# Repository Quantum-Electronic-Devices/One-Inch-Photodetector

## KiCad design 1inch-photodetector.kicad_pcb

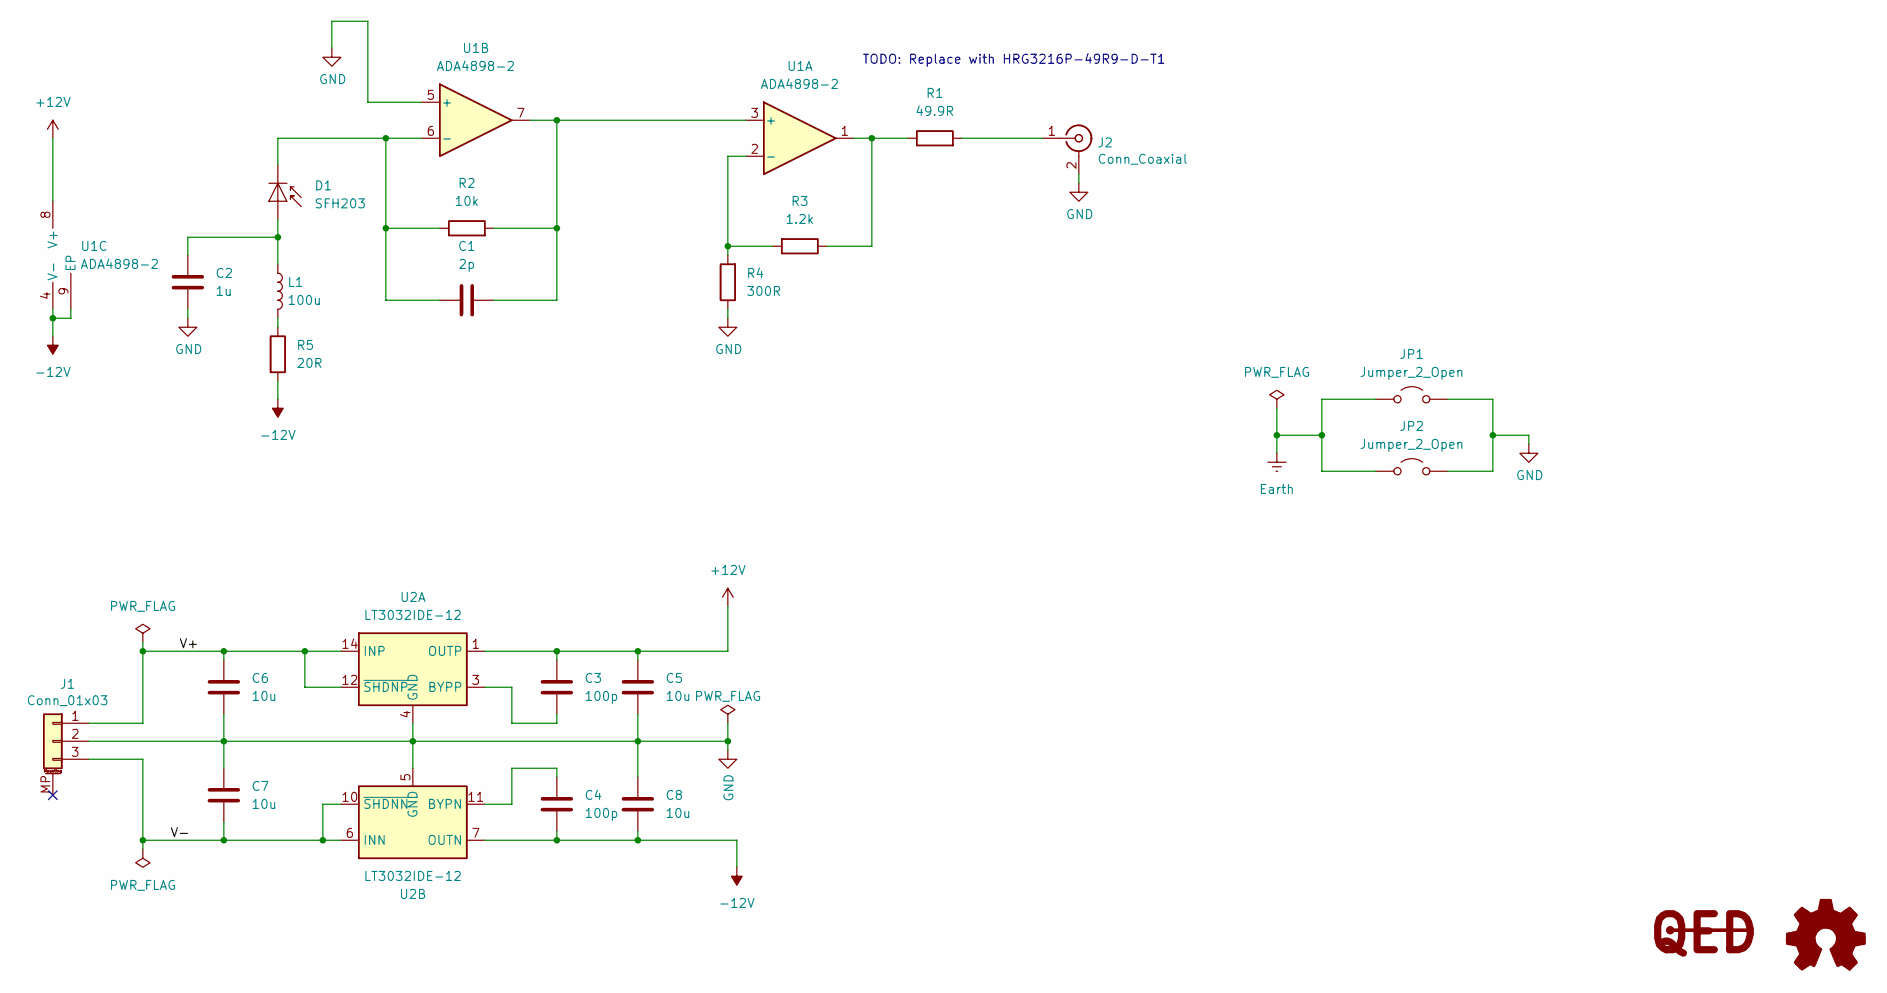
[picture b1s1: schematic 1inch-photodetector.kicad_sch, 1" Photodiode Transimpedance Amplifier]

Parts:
C1: 2p; C_0603_1608Metric
C2: 1u; C_0603_1608Metric
C3, C4: 100p; C_0603_1608Metric
C5, C6, C7, C8: 10u; C_0805_2012Metric
D1: SFH203; LED_D5.0mm_IRGrey
J1: Conn_01x03; Molex_PicoBlade_53398-0371_1x03-1MP_P1.25mm_Vertical
J2: Conn_Coaxial; SMP_TE_CONSMP001-SMD-G-T_Vertical
JP1, JP2: Jumper_2_Open; R_0402_1005Metric
L1: 100u; L_0805_2012Metric
LOGO1: Logo_Open_Hardware_Large; OSHW-Logo_7.5x8mm_SilkScreen
R1: 49.9R; R_1206_3216Metric
R2: 10k; R_0603_1608Metric
R3: 1.2k; R_0603_1608Metric
R4: 300R; R_0603_1608Metric
R5: 20R; R_0603_1608Metric
SYM1: Logo_QED; QED-logo_small
U1: ADA4898-2; SOIC-8-1EP_3.9x4.9mm_P1.27mm_EP2.41x3.81mm
U2: LT3032IDE-12; Linear_DE14MA

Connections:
+12V: C3.1, C5.1, U1.8 (V+), U2.1 (OUTP)
-12V: C4.2, C8.2, R5.2, U1.4 (V-), U1.9 (EP), U2.7 (OUTN)
/V+: C6.1, J1.1, U2.12 (~SHDNP), U2.14 (INP)
/V-: C7.2, J1.3, U2.6 (INN), U2.9 (INN), U2.10 (~SHDNN)
Earth: JP1.1 (A), JP2.1 (A)
GND: C2.2, C5.2, C6.2, C7.1, C8.1, J1.2, J2.2 (Ext), JP1.2 (B), JP2.2 (B), R4.1, U1.5 (+), U2.4 (GND), U2.5 (GND)
unnamed: C2.1, D1.2 (A), L1.1
unnamed: C1.1, D1.1 (K), R2.1, U1.6 (-)
unnamed: J2.1 (In), R1.2
unnamed: L1.2, R5.1
unnamed: R1.1, R3.1, U1.1
unnamed: C1.2, R2.2, U1.3 (+), U1.7
unnamed: R3.2, R4.2, U1.2 (-)
unnamed: C3.2, U2.3 (BYPP)
unnamed: C4.1, U2.11 (BYPN)

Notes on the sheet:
TODO: Replace with HRG3216P-49R9-D-T1

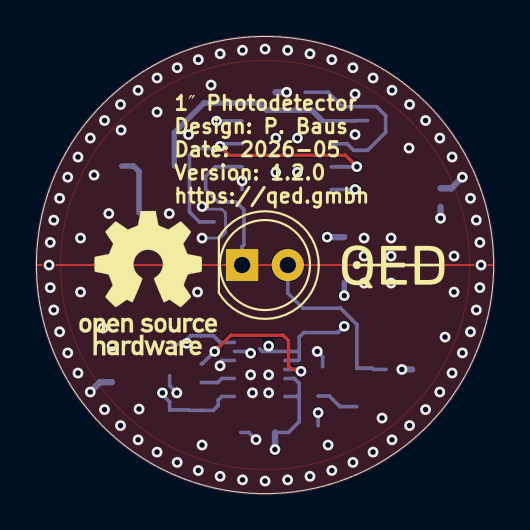
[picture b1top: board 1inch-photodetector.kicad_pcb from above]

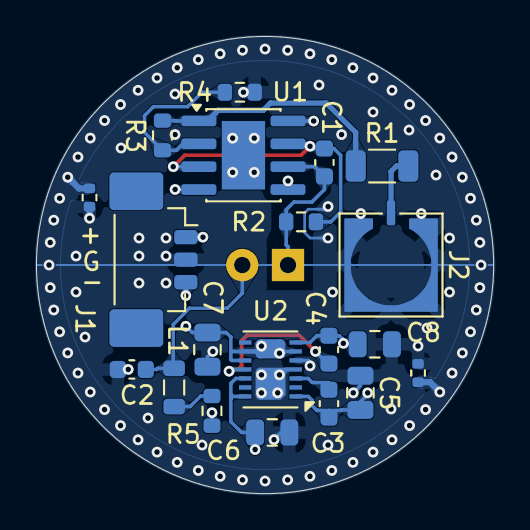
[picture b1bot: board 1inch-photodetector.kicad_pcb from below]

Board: 4 copper layers, 25.4 x 25.4 mm, 23 parts (20 on the bottom side), 15 nets.

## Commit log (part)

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2025-11-25 Bump KiBot to v9
2025-11-25 Cleanup
2025-11-25 [gha] Bump actions/download-artifact from 4 to 6
    Bumps [actions/download-artifact](https://github.com/actions/download-artifact) from 4 to 6.
    - [Release notes](https://github.com/actions/download-artifact/releases)
    - [Commits](https://github.com/actions/download-artifact/compare/v4...v6)
    ---
    updated-dependencies:
    - dependency-name: actions/download-artifact
2025-11-25 Update logo
2025-11-25 [gha] Bump actions/upload-artifact from 4 to 5
    Bumps [actions/upload-artifact](https://github.com/actions/upload-artifact) from 4 to 5.
    - [Release notes](https://github.com/actions/upload-artifact/releases)
    - [Commits](https://github.com/actions/upload-artifact/compare/v4...v5)
    ---
    updated-dependencies:
    - dependency-name: actions/upload-artifact
2025-11-25 Changed QED logo to polygon to make it independent of the font of the host system
2025-11-25 Add copyright notice to logo
2025-11-25 Remove QED text from silkscreen
2025-11-25 Update logo copyright
2025-11-25 Added QED URL to version text
2025-12-12 [gha] Bump actions/upload-artifact from 5 to 6
    Bumps [actions/upload-artifact](https://github.com/actions/upload-artifact) from 5 to 6.
    - [Release notes](https://github.com/actions/upload-artifact/releases)
    - [Commits](https://github.com/actions/upload-artifact/compare/v5...v6)
    ---
    updated-dependencies:
    - dependency-name: actions/upload-artifact
2025-12-12 [gha] Bump actions/download-artifact from 6 to 7
    Bumps [actions/download-artifact](https://github.com/actions/download-artifact) from 6 to 7.
    - [Release notes](https://github.com/actions/download-artifact/releases)
    - [Commits](https://github.com/actions/download-artifact/compare/v6...v7)
    ---
    updated-dependencies:
    - dependency-name: actions/download-artifact
2025-12-17 Bump libraries from `ba5563d` to `d79317d`
    Bumps [libraries](https://github.com/PatrickBaus/KiCad-libraries) from `ba5563d` to `d79317d`.
    - [Commits](https://github.com/PatrickBaus/KiCad-libraries/compare/ba5563d66c23dea06d561adcb039ddac5a03efdf...d79317d926704a58090a36fac06bfafa731a048b)
    ---
    updated-dependencies:
    - dependency-name: libraries
    dependency-version: d79317d926704a58090a36fac06bfafa731a048b
2026-02-26 [gha] Bump actions/upload-artifact from 5 to 7
    Bumps [actions/upload-artifact](https://github.com/actions/upload-artifact) from 5 to 7.
    - [Release notes](https://github.com/actions/upload-artifact/releases)
    - [Commits](https://github.com/actions/upload-artifact/compare/v5...v7)
    ---
    updated-dependencies:
    - dependency-name: actions/upload-artifact
2026-02-26 [gha] Bump actions/download-artifact from 6 to 8
    Bumps [actions/download-artifact](https://github.com/actions/download-artifact) from 6 to 8.
    - [Release notes](https://github.com/actions/download-artifact/releases)
    - [Commits](https://github.com/actions/download-artifact/compare/v6...v8)
    ---
    updated-dependencies:
    - dependency-name: actions/download-artifact
2026-02-28 Bump footprints to latest
2026-02-28 Add comments regarding tolerances
2026-02-28 Fixed white spaces
2026-02-28 Disconnect GND from Earth by default (#10)
    * Removed GND-Earth connection
    - Added optional jumpers to connect GND to Earth
    - Added more ground stitching vias
    * Increased size to 25.4 mm
    * Added comments regarding tolerances
2026-02-28 [gha] Bump actions/upload-artifact from 5 to 7 (#8)
    Bumps [actions/upload-artifact](https://github.com/actions/upload-artifact) from 5 to 7.
    - [Release notes](https://github.com/actions/upload-artifact/releases)
    - [Commits](https://github.com/actions/upload-artifact/compare/v5...v7)
    ---
    updated-dependencies:
    - dependency-name: actions/upload-artifact
2026-02-28 Bump libraries from `ba5563d` to `4179135` (#7)
    Bumps [libraries](https://github.com/PatrickBaus/KiCad-libraries) from `ba5563d` to `4179135`.
    - [Commits](https://github.com/PatrickBaus/KiCad-libraries/compare/ba5563d66c23dea06d561adcb039ddac5a03efdf...41791358010d2de5d2401e25bd30de257630acf6)
    ---
    updated-dependencies:
    - dependency-name: libraries
    dependency-version: 41791358010d2de5d2401e25bd30de257630acf6
2026-02-28 Added stackup to gerber files
2026-02-28 Added stackup to gerber files (#11)
2026-02-28 Bump version to 1.1.0
2026-03-01 Fix intermittend GHA ref_name is empty issue. See https://github.com/actions/runner/issues/2788
2026-03-01 Cleanup/remove old refs (#13)
    * Removed TODOs that where done
    - Fixed R1 MFN
    * Added gerber_files folder to gitignore
2026-03-02 Fix stackup. An incorrect stackup was given. Changed to PCBWay/JLCPCB standard. (#16)
    - Bump version to 1.1.1
2026-03-02 Update CI to reusable workflow
2026-03-02 Fixed typo
2026-03-02 Add CI check to test for revision label
2026-03-02 Fix Regex
2026-03-02 Fix revision label (#18)
    * Fixed PCB revision label. Bump to 1.1.1
    * Add CI check to test for revision label
2026-03-02 Fixed CI permission issues with uploading files
2026-03-02 Fixed CI permission issues with uploading files (#19)
2026-03-02 Run workflow if any action is changed
2026-03-02 Use github.event.release.tag_name instead of github.ref_name
2026-03-02 Use github.event.release.tag_name instead of github.ref_name (#21)
    This fixes https://github.com/actions/runner/issues/2788
2026-03-02 Escape filenames in CI job (#23)
2026-03-02 Bump GitHub actions
2026-03-02 Bump QED logo to latest
2026-03-02 Renamed custom footprint lib
2026-05-26 Add initial datasheet draft
2026-05-26 Added CI to build the datasheet
2026-05-26 Added CI for periodic visual diffs
2026-05-26 Update gitignore file for KiCad 10 (#26)
2026-05-26 Bump CI
2026-05-26 Bump version text on silkscreen
2026-05-26 Use dev version of KiBot
2026-05-26 [gha] Bump actions/upload-artifact from 4 to 7
    Bumps [actions/upload-artifact](https://github.com/actions/upload-artifact) from 4 to 7.
    - [Release notes](https://github.com/actions/upload-artifact/releases)
    - [Commits](https://github.com/actions/upload-artifact/compare/v4...v7)
    ---
    updated-dependencies:
    - dependency-name: actions/upload-artifact
2026-05-26 Add missing images
2026-05-26 [gha] Bump actions/upload-artifact from 4 to 7 (#30)
    Bumps [actions/upload-artifact](https://github.com/actions/upload-artifact) from 4 to 7.
    - [Release notes](https://github.com/actions/upload-artifact/releases)
    - [Commits](https://github.com/actions/upload-artifact/compare/v4...v7)
    ---
    updated-dependencies:
    - dependency-name: actions/upload-artifact
2026-05-26 Fixed typo in GH action (#32)
2026-05-26 Refactored datasheet GH CI workflow
    - Split compiling and uploading of the PDF
2026-06-18 [gha] Bump actions/checkout from 6 to 7
    Bumps [actions/checkout](https://github.com/actions/checkout) from 6 to 7.
    - [Release notes](https://github.com/actions/checkout/releases)
    - [Changelog](https://github.com/actions/checkout/blob/main/CHANGELOG.md)
    - [Commits](https://github.com/actions/checkout/compare/v6...v7)
    ---
    updated-dependencies:
2026-06-30 [gha] Bump actions/checkout from 6 to 7 (#33)
    Bumps [actions/checkout](https://github.com/actions/checkout) from 6 to 7.
    - [Release notes](https://github.com/actions/checkout/releases)
    - [Changelog](https://github.com/actions/checkout/blob/main/CHANGELOG.md)
    - [Commits](https://github.com/actions/checkout/compare/v6...v7)
    ---
    updated-dependencies:

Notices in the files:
1inch-photodetector.kicad_pcb:
Copyright (©) 2026, Patrick Baus
Licensed under CERN OHL-W v2.0
1inch-photodetector.kicad_sch:
Copyright (©) 2025, Patrick Baus
parts and their libraries:
Copyright Quantum Electronic Devices GmbH
Copyright Quantum Electronic Devices
